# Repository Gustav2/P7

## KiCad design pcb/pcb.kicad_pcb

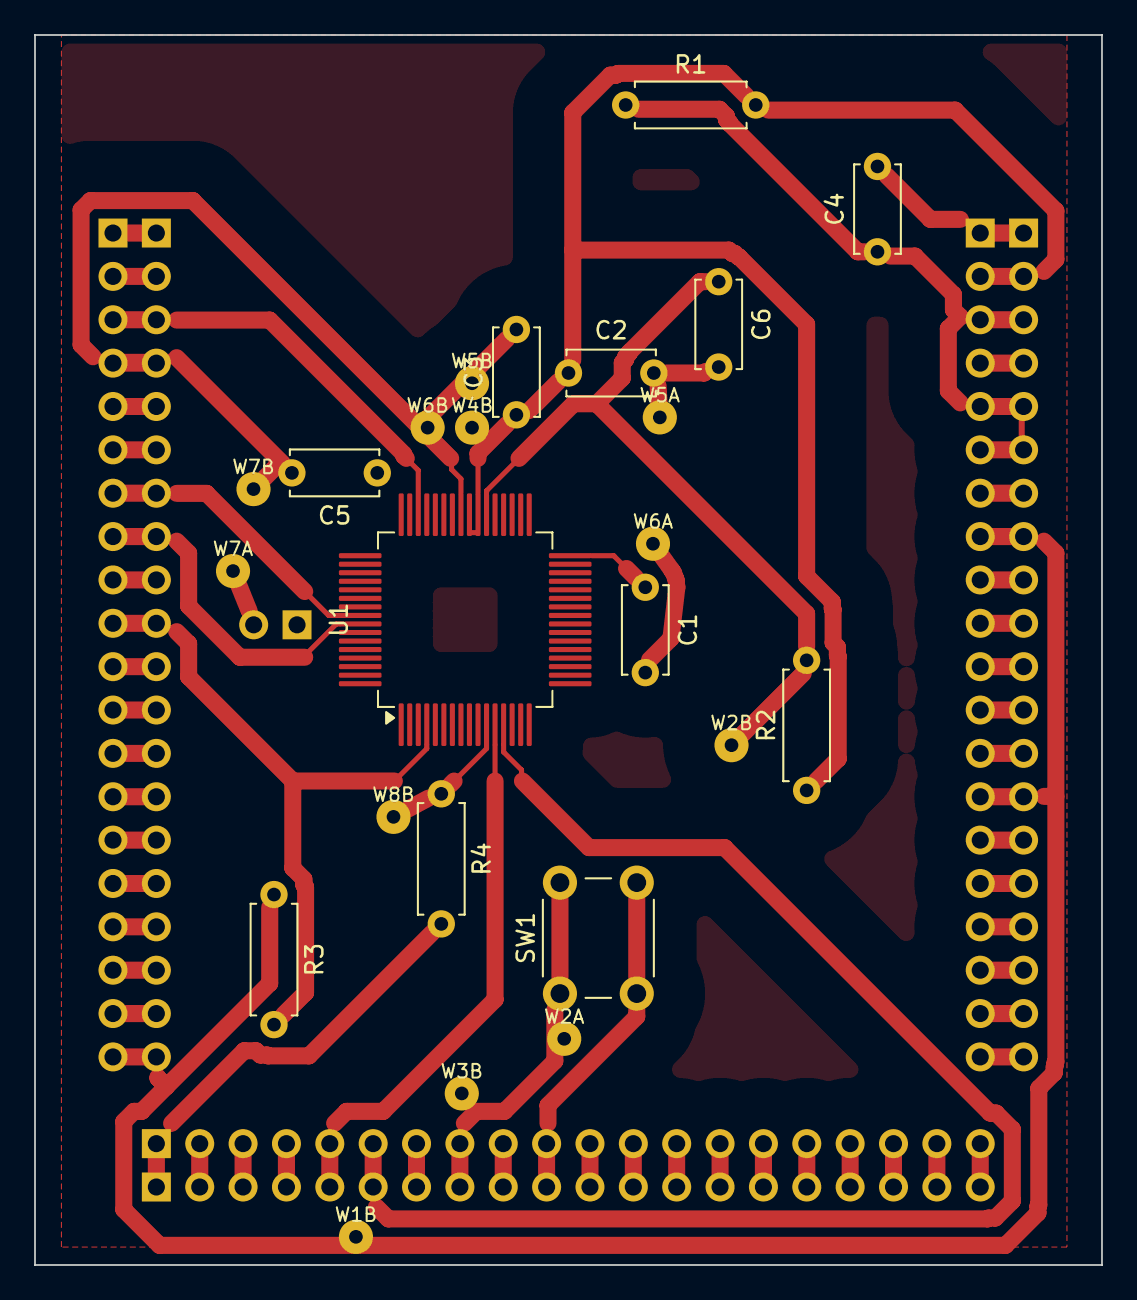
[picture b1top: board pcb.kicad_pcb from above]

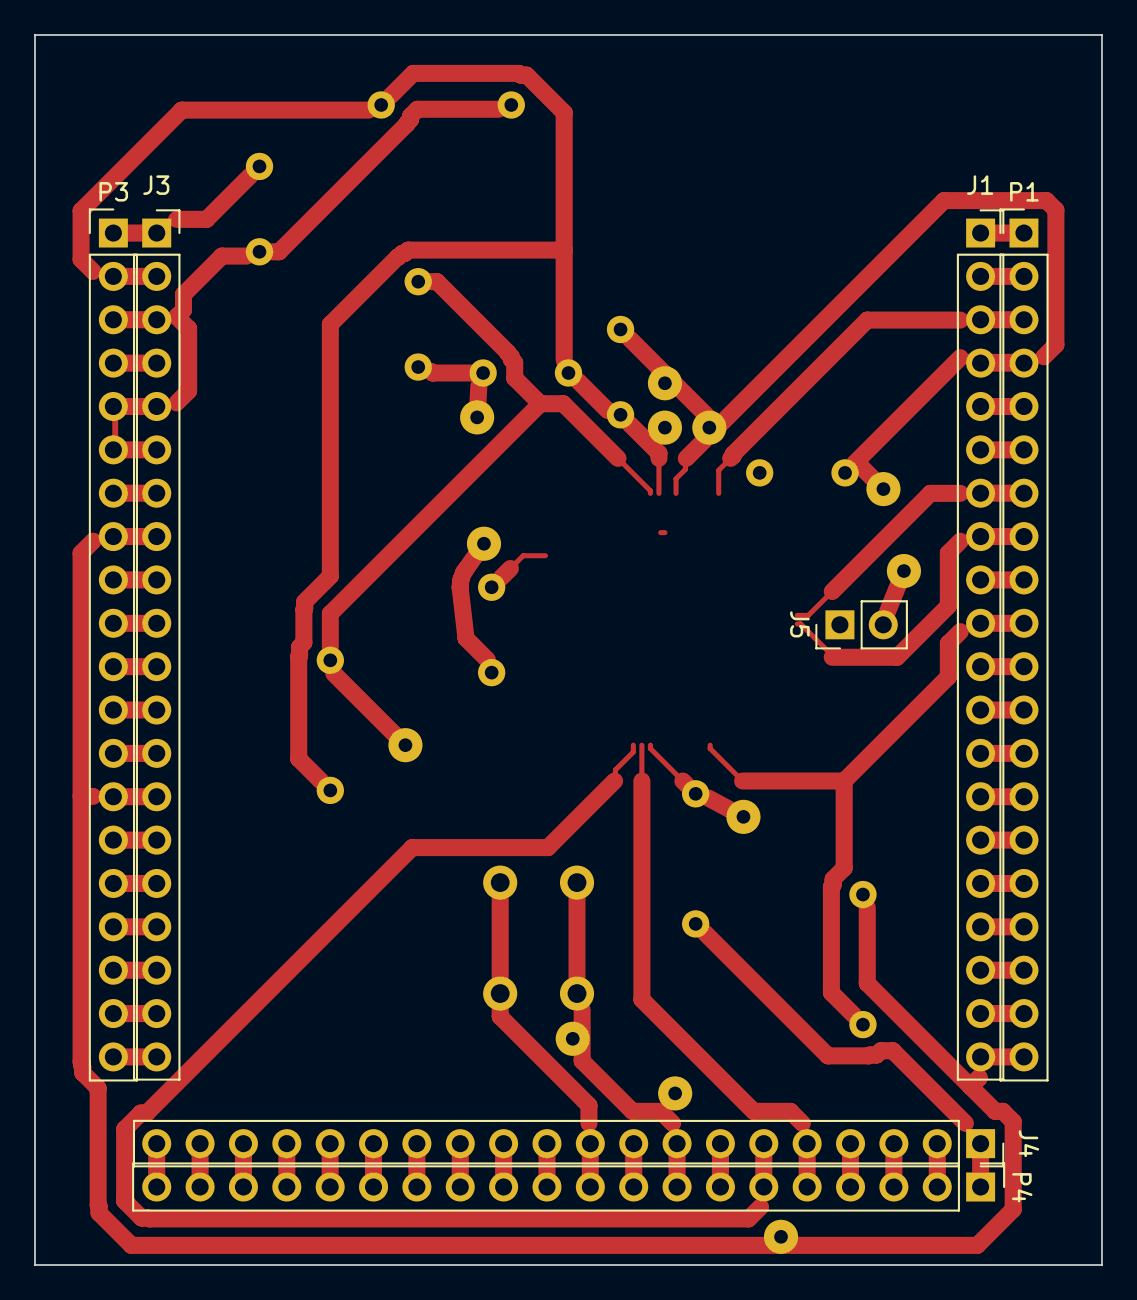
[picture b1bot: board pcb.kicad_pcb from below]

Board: 2 copper layers, 62.5 x 72.0 mm, 31 parts (7 on the bottom side), 42 nets.

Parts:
C1: 470nF; C_Disc_D5.0mm_W2.5mm_P5.00mm
C2: 10uF; C_Disc_D5.0mm_W2.5mm_P5.00mm
C3: 100nF; C_Disc_D5.0mm_W2.5mm_P5.00mm
C4: 4.7uF; C_Disc_D5.0mm_W2.5mm_P5.00mm
C5: 1uF; C_Disc_D5.0mm_W2.5mm_P5.00mm
C6: 10nF; C_Disc_D5.0mm_W2.5mm_P5.00mm
J1: CW308_WEST; PinSocket_1x20_P2.54mm_Vertical
J3: CW308_EAST; PinSocket_1x20_P2.54mm_Vertical
J4: CW308_SOUTH; PinSocket_1x20_P2.54mm_Vertical
J5: BSL_GND; PinHeader_1x02_P2.54mm_Vertical
P1: WEST_PINS; PinHeader_1x20_P2.54mm_Vertical
P3: EAST_PINS; PinHeader_1x20_P2.54mm_Vertical
P4: SOUTH_PINS; PinHeader_1x20_P2.54mm_Vertical
R1: 10R; R_Axial_DIN0207_L6.3mm_D2.5mm_P7.62mm_Horizontal
R2, R4: 47k; R_Axial_DIN0207_L6.3mm_D2.5mm_P7.62mm_Horizontal
R3: 4.7k; R_Axial_DIN0207_L6.3mm_D2.5mm_P7.62mm_Horizontal
SW1: RESET; SW_PUSH_6mm
U1: MSPM0L2228SPMR; LQFP-64_10x10mm_P0.5mm
W1B, W2A, W2B, W3B, W4B, W5A, W5B, W6A, W6B, W7A, W7B, W8B: Wire

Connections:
/TRIG: J1.10, P1.10, R3.2, U1.4 (PB16)
unnamed: J1.1, P1.1
unnamed: J1.3, P1.3, U1.46 (PA6)
unnamed: J1.5, P1.5
unnamed: J1.7, P1.7, U1.56 (PA10/BSL_TX)
unnamed: J1.8, P1.8, U1.57 (PA11/BSL_RX)
unnamed: J1.9, P1.9
unnamed: C6.1, J1.11, J4.8, P1.11, P4.8, R2.2, SW1.1, U1.38 (NRST), W2A.1, W2B.1, W3B.1
unnamed: J1.12, P1.12
unnamed: J1.13, P1.13
unnamed: J1.14, P1.14
unnamed: C1.2, C2.2, C3.2, C4.2, C5.2, C6.2, J1.2, J1.4, J1.6, J1.15, J1.16, J3.1, J3.4, J3.7, J3.9, J3.10, J3.16, J3.17, J4.1, J4.9, J4.10, J5.2, P1.2, P1.4, P1.6, P1.15, P1.16, P3.1, P3.4, P3.7, P3.9, P3.10, P3.16, P3.17, P4.1, P4.9, P4.10, R4.2, SW1.2, U1.41 (VSS), W5A.1, W5B.1, W6A.1, W6B.1, W7A.1, W7B.1
unnamed: J1.17, P1.17
unnamed: J1.18, P1.18
unnamed: J1.19, P1.19
unnamed: J1.20, J3.8, J3.14, J4.7, P1.20, P3.8, P3.14, P4.7, R3.1, W1B.1
unnamed: C2.1, C3.1, C5.1, J3.2, P3.2, R1.2, R2.1, U1.39 (VBAT), U1.40 (VDD), W4B.1
unnamed: C4.1, J3.3, J3.5, J3.6, P3.3, P3.5, P3.6, R1.1
unnamed: J3.11, P3.11
unnamed: J3.12, P3.12
unnamed: J3.13, P3.13
unnamed: J3.15, P3.15
unnamed: J3.18, P3.18
unnamed: J3.19, P3.19
unnamed: J3.20, P3.20
unnamed: J4.2, P4.2
unnamed: J4.3, P4.3
unnamed: J4.4, P4.4
unnamed: J4.5, P4.5, U1.12 (PA19/SWDIO)
unnamed: J4.6, P4.6, U1.13 (PA20/SWCLK)
unnamed: J4.11, P4.11
unnamed: J4.12, P4.12
unnamed: J4.13, P4.13
unnamed: J4.14, P4.14
unnamed: J4.15, P4.15
unnamed: J4.16, P4.16
unnamed: J4.17, P4.17
unnamed: J4.18, P4.18
unnamed: J4.19, P4.19
unnamed: J4.20, P4.20
unnamed: J5.1, R4.1, U1.11 (PA18/BSL_INVOKE), W8B.1
unnamed: C1.1, U1.32 (VCORE)

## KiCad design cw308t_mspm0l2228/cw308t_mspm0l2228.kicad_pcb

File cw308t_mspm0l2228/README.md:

# CW308T-MSPM0L2228 — SCA target hat (2-layer)

A ChipWhisperer target board for the TI **MSPM0L2228** (LQFP-80, TI PN0080A: 12×12 mm body, 0.5 mm pitch), built to drop onto the
**CW308T→CW312 adapter** and attack the AES-ADV engine with a clean measurement front-end.

## Geometry — matches the CW308T→CW312 adapter
Connector positions, mounting holes and outline are taken from NewAE's **CW308T_toCW312T**
gerbers (the "2-layer solid board" adapter): board **2.32″ × 2.8″ (58.9 × 71.1 mm)** matching the adapter's main body, the three
20-pin connectors on West/East/South edges (West↔East centres 1.9″, South row 0.2″ below the
side columns), 3× M3 mounting holes at the adapter positions.

## Connectors (per your spec)
- **Female 1×20 sockets on the BOTTOM** (J1 West, J3 East, J4 South) — mate **down** onto the
  adapter at the exact CW308 positions.
- **Male 1×20 breakout headers on the TOP** (P1/P3/P4), **outboard of the sockets (toward the edges)**, **all 60 pins**
  duplicated 1:1 with the sockets — plug in cables/probes from above. Sockets and the 3 M3 holes are placed at the adapter's exact absolute positions, so it drops straight on.
- Debug: **J_SWD** (Cortex 2×5 SWD), **SW1** reset, **TP_BSL** (PA18).

## Electrical
- **Debug header J_DBG** (1x8, 2.54 mm, same pins as the connectors), left->right: 3V3, GND, SWDIO, SWCLK, TXD, RXD, RST, BSL. Reset button SW1. Copper label "WolfSniff - Group 741" engraved in the top copper.
- **2-layer, plated vias**, GND **pour on both layers** (10 vias). Traces: power/analog 0.4 mm (necked to 0.3 mm at the chip), logic signals 0.3 mm (the 0.5 mm-pitch QFP pads are 0.25 mm wide). No traces or vias under the chip body. Vias are **1.0 mm drilled, pin-through** (1.4 mm copper, plated both sides) so a pin/wire can be pushed through and soldered on both layers. Pour-to-feature isolation 0.8 mm (CNC clears wide channels around every trace/pad).
- **Decoupling caps hard against the chip pins**: C1 470nF at VCORE(80), C2/C5 at VDD/VBAT(8/9/7),
  C3 at VDD2(49), C4 4.7µF bulk (supply side). R1 (0Ω shunt) / R2 (nRST pull-up) are DNP options.
- Pin map: TRIG=PA0, UART=PA10/PA11, ext-clock=PA6/HFCLK_IN, SWDIO/SWCLK=PA19/PA20, VCORE=pin80.

## Files
- `cw308t_mspm0l2228.kicad_pcb` — routed + poured PCB (KiCad 9). **Authoritative.**
- `cnc/` + `cw308t_mspm0l2228_cnc.zip` — your CAM set:
  `TopLayer.gbr`, `BottomLayer.gbr`, `BoardOutline.gbr`, `DrillPlated.drl` (147 holes: all 120
  connector pins + 8-pin debug header + 10 vias, all plated 1.0 mm), `DrillUnplated.drl` (3× M3).
- `gerbers/` + `cw308t_mspm0l2228_gerbers.zip` — full RS-274X set + drill map (for a fab house).
- `render_top.png`, `render_bottom.png` — 3D previews.
- `BOM.csv`.

## Verify before cutting / ordering
1. DRC is clean (0 unconnected, 0 clearance/hole). The only DRC notes are **courtyard keep-out
   overlaps** where the socket+male pairs sit 0.1″ apart and at the connector corners — expected
   on a board this dense; the actual copper/holes all clear.
2. **Connector pin-1 orientation**: the sockets are bottom-mounted, so confirm pin 1 of each
   socket lands on the adapter's pin 1 (check against the adapter silk). If a connector is
   reversed it's a one-line fix in the generator.
3. The GND pour is filled in the gerbers. If you edit in KiCad, press `B` to re-fill before
   re-exporting.

## Note
The `.kicad_sch` is the earlier logical schematic; the **PCB is authoritative** for this build
(the sockets/males/pass-throughs are a physical breakout, not a change to the logical nets).

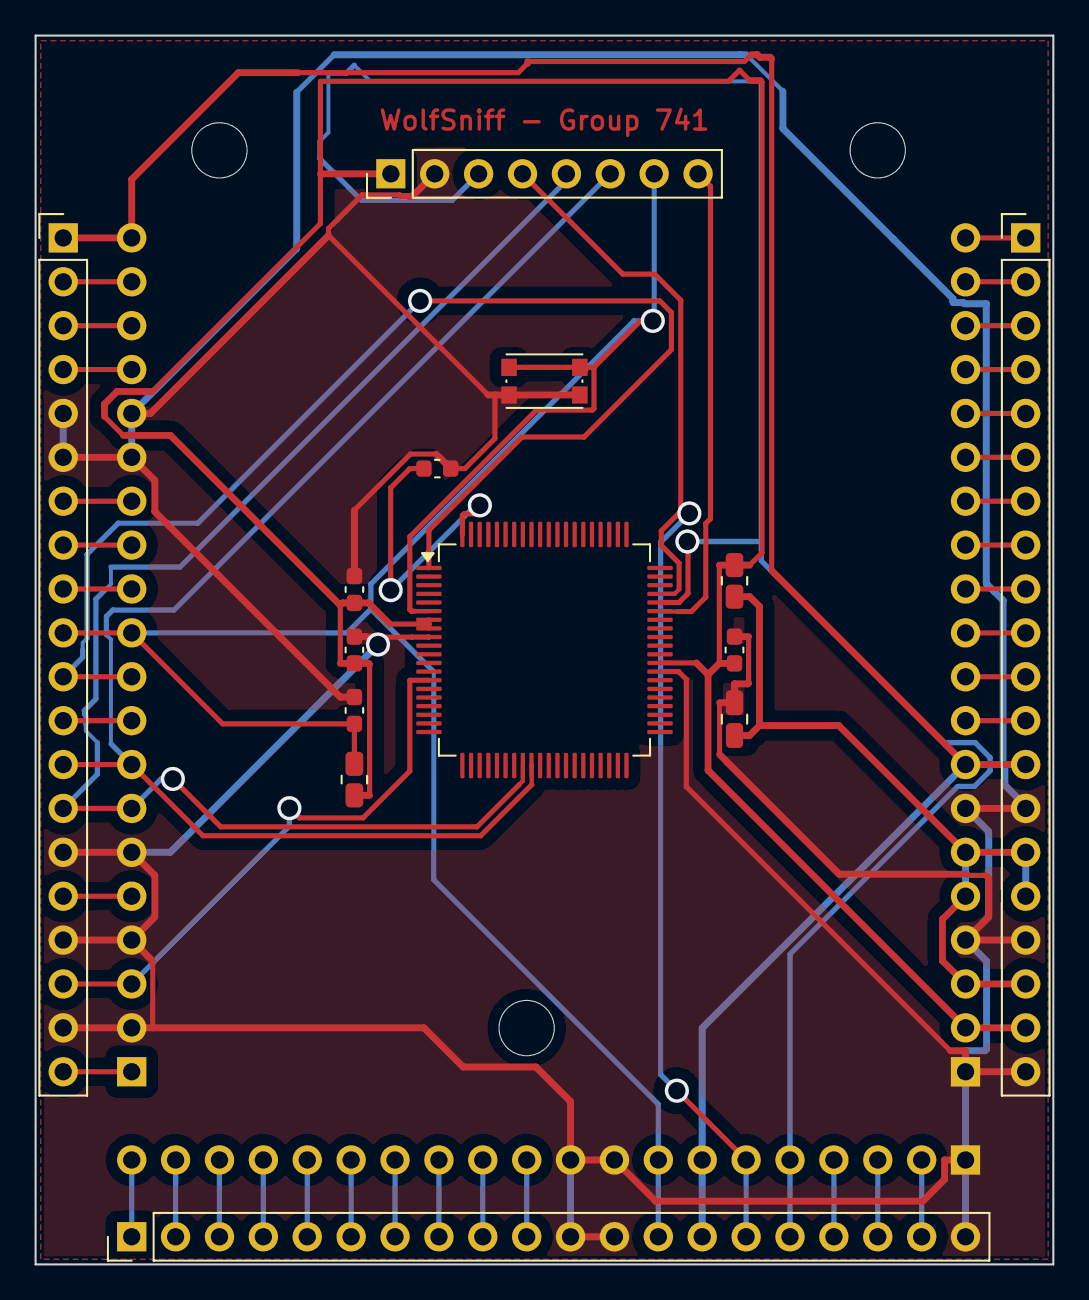
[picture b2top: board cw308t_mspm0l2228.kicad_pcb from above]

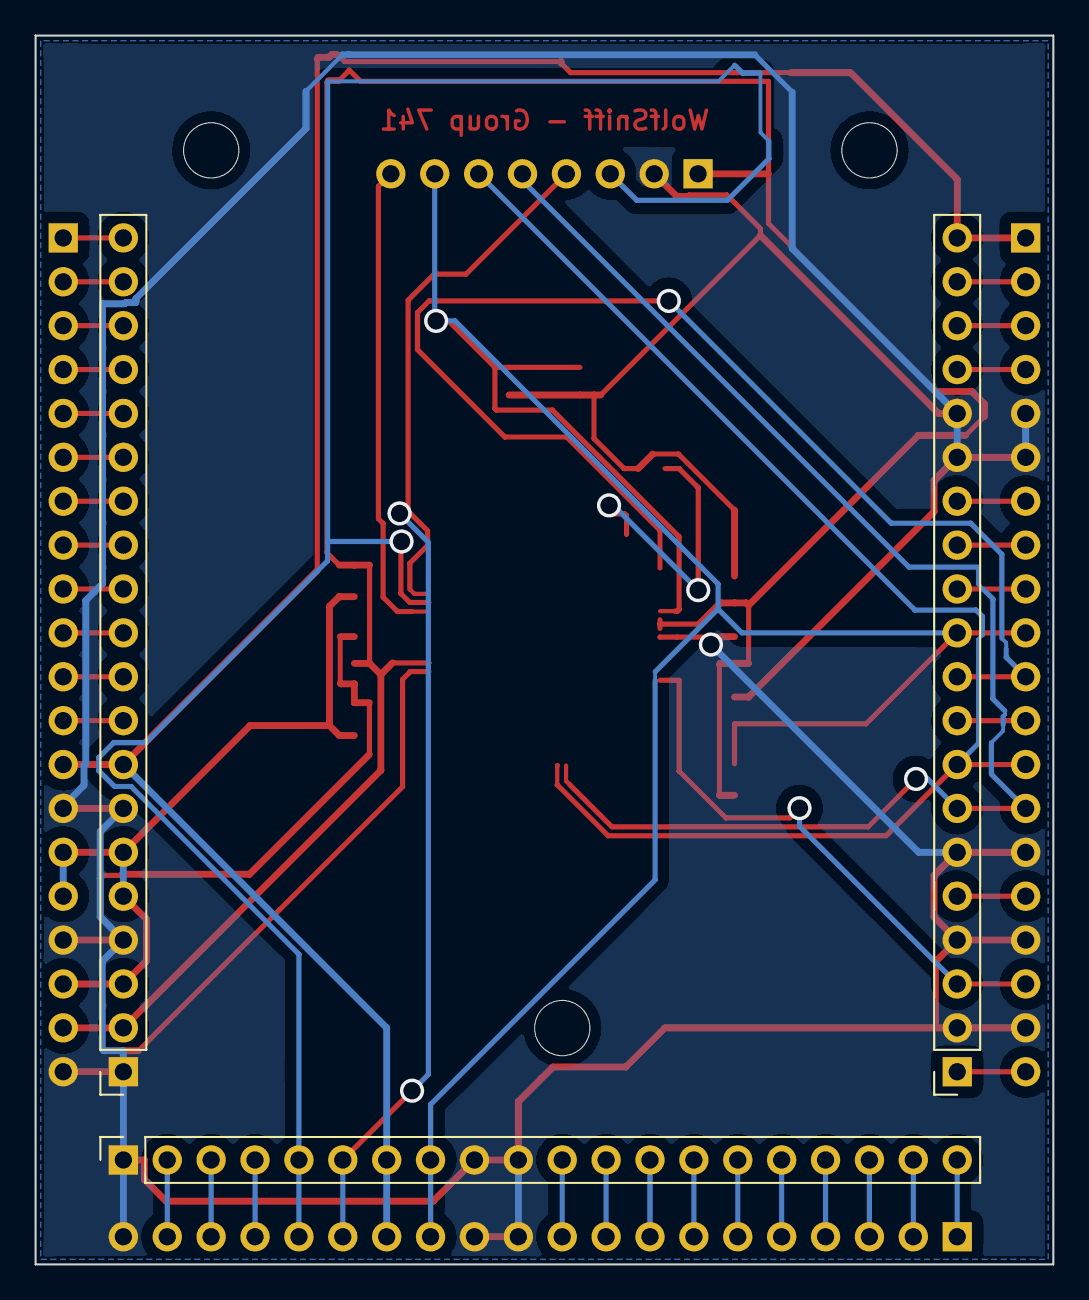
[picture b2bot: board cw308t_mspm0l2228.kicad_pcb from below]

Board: 2 copper layers, 58.9 x 71.1 mm, 20 parts (3 on the bottom side), 47 nets.

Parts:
C1: 470nF; C_0603_1608Metric
C2, C3, C5: 100nF; C_0603_1608Metric
C4: 4.7uF; C_0805_2012Metric
C6: 100nF_DNP; C_0603_1608Metric
HOLE1, HOLE2, HOLE3: M3; MountingHole_3.2mm_M3
J1: CW308_WEST_A; PinSocket_1x20_P2.54mm_Vertical
J3: CW308_EAST_C; PinSocket_1x20_P2.54mm_Vertical
J4: CW308_SOUTH_B; PinSocket_1x20_P2.54mm_Vertical
J_DBG: DEBUG; PinHeader_1x08_P2.54mm_Vertical
P1: WEST_BRK; PinHeader_1x20_P2.54mm_Vertical
P3: EAST_BRK; PinHeader_1x20_P2.54mm_Vertical
P4: SOUTH_BRK; PinHeader_1x20_P2.54mm_Vertical
R1: 0R_shunt_DNP; R_0805_2012Metric
R2: 10k_DNP; R_0805_2012Metric
SW1: RESET; SW_Push_1P1T_NO_CK_KMR2
U1: MSPM0L2228SPN; LQFP-80_12x12mm_P0.5mm

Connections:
BSL: J_DBG.8, U1.55
CLKIN: J1.3, P1.18, U1.14
FILT_OUT: C4.1, J3.3, J3.5, J3.6, P3.15, P3.16, P3.18, R1.1
GND: C1.2, C2.2, C3.2, C4.2, C5.2, C6.2, J1.2, J1.4, J1.6, J1.15, J1.16, J3.1, J3.4, J3.7, J4.1, J4.9, J4.10, J_DBG.2, P1.5, P1.6, P1.15, P1.17, P1.19, P3.14, P3.17, P3.20, P4.11, P4.12, P4.20, SW1.2, U1.9, U1.48
SP_E9: J3.9, P3.12
SP_E10: J3.10, P3.11
SP_E11: J3.11, P3.10
SP_E12: J3.12, P3.9
SP_E13: J3.13, P3.8
SP_E14: J3.14, P3.7
SP_E15: J3.15, P3.6
SP_E16: J3.16, P3.5
SP_E17: J3.17, P3.4
SP_E18: J3.18, P3.3
SP_E19: J3.19, P3.2
SP_E20: J3.20, P3.1
SP_S2: J4.2, P4.19
SP_S3: J4.3, P4.18
SP_S4: J4.4, P4.17
SP_S11: J4.11, P4.10
SP_S12: J4.12, P4.9
SP_S13: J4.13, P4.8
SP_S14: J4.14, P4.7
SP_S15: J4.15, P4.6
SP_S16: J4.16, P4.5
SP_S17: J4.17, P4.4
SP_S18: J4.18, P4.3
SP_S19: J4.19, P4.2
SP_S20: J4.20, P4.1
SP_W1: J1.1, P1.20
SP_W5: J1.5, P1.16
SP_W9: J1.9, P1.12
SP_W12: J1.12, P1.9
SP_W13: J1.13, P1.8
SP_W14: J1.14, P1.7
SP_W17: J1.17, P1.4
SP_W18: J1.18, P1.3
SP_W19: J1.19, P1.2
SWCLK: J4.6, J_DBG.4, P4.15, U1.57
SWDIO: J4.5, J_DBG.3, P4.16, U1.56
TRIG: J1.10, P1.11, U1.1
UART_RX: J1.8, J_DBG.6, P1.13, U1.29
UART_TX: J1.7, J_DBG.5, P1.14, U1.28
VCORE: C1.1, U1.80
VDD_CHIP: C2.1, C3.1, C5.1, J3.2, J_DBG.1, P3.19, R1.2, R2.1, U1.7, U1.8, U1.49
VREF_SUPPLY: J1.20, J3.8, J4.7, P1.1, P3.13, P4.14
nRST: C6.1, J1.11, J4.8, J_DBG.7, P1.10, P4.13, R2.2, SW1.1, U1.6

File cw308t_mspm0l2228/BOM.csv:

Ref,Qty,Value,Footprint,Populate,Notes
U1,1,MSPM0L2228SPN,LQFP-80 14x14 0.65mm,YES,Target MCU
C1,1,470nF,0603,YES,VCORE (pin 80) - required, hard against the pin
C2,1,100nF,0603,YES,VDD/VSS (pin 8/9)
C5,1,100nF,0603,YES,VBAT (pin 7)
C3,1,100nF,0603,YES,VDD2 (pin 49)
C4,1,4.7uF,0805,YES,Bulk (supply side of shunt)
C6,1,100nF,0603,NO (DNP),Optional nRST cap
R1,1,0R,0805,NO (DNP),Optional local shunt
R2,1,10k,0805,NO (DNP),Optional nRST pull-up
J1/J3/J4,3,PinSocket 1x20 2.54mm,female vertical (BOTTOM),YES,CW308 West/East/South sockets - mate down onto adapter
P1/P3/P4,3,PinHeader 1x20 2.54mm,male vertical (TOP),YES,All-60 breakout headers (offset 0.1in) for cables
J_SWD,1,Cortex 2x5 1.27mm,PinHeader 2x05,YES,SWD debug
SW1,1,Reset,SW KMR2 SMD,YES,nRST button
TP_BSL,1,BSL,TestPoint 1.5mm,OPTIONAL,PA18 BSL test point
HOLE1-3,3,M3,3.2mm,YES,Mounting (adapter positions)
